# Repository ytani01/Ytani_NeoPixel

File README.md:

# Ytani NeoPixel Library

## 1. for Python3 on Raspberry Pi
  [rpi-python3/](rpi-python3/)

## 2. for C++ on Arduino, ESP32, ATTiny etc..
  [arduino-etc/](arduino-etc/)

### 2.0 !! 重要 !!

* NeoPixelライブラリの実行で、割り込みが効かなくなる
  ``show()``の直後に、``interrupts()`` または ``sei()``をすること！
* ATTiny85のメモリ(RAM)不足で、挙動がおかしくなる。

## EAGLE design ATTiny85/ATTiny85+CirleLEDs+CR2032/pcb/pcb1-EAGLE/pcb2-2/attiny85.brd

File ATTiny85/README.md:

# ATTiny85

## Arduio IEDによる書き込み

### ブートローダー

### ボード設定

- [ツール]-[ボード]-[ATTinyCore]-[ATTiny25/45/85 (No bootloader)]
- [ツール]-[Chip]-[ATTiny85]
- [ツール]-[書き込み装置]-[Arduino Leo/Micro as ISP (ATmega32U4)]

### ブートローダーの書き込み (最初の一回だけ)

- [ツール]-[ブートローダーを書き込む]

### 書き込み

- [スケッチ]-[書き込み装置を使って書き込む] (Ctrl+Shift+U)

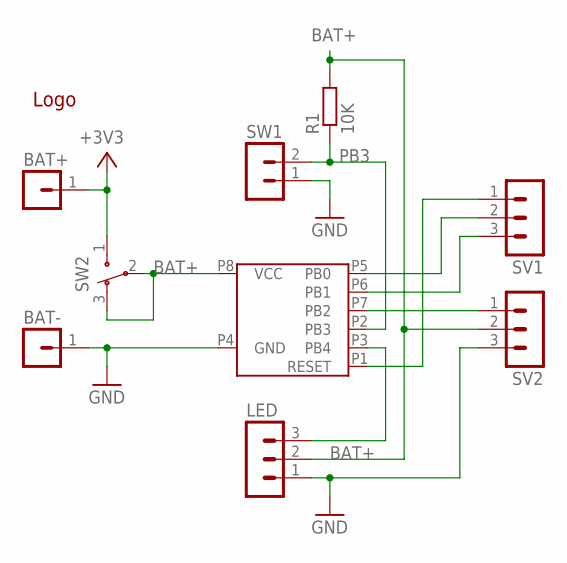
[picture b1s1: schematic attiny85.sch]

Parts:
ATTINY85-1: ATTINY85SOP8; ATTINY85-20SUR
BAT+: PINHEAD-MA01-1
BAT-: PINHEAD-MA01-1
LED: PINHEAD-MA03-1
LOGO1: LOGO-YTLOGO2-BOTTOM; LOGO-YT2-BOTTOM
R1: 10K; M3216
SV1, SV2: PINHEAD-MA03-1
SW1: PINHEAD-MA02-1
SW2: SW3-1

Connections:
+3V3: BAT+.1, SW2.1
BAT+: ATTINY85-1.P8 (VCC), LED.2, R1.2, SV2.2, SW2.2, SW2.3
GND: ATTINY85-1.P4 (GND), BAT-.1, LED.1, SV2.3, SW1.1
unnamed: ATTINY85-1.P3 (PB4), LED.3
unnamed: ATTINY85-1.P7 (PB2), SV2.1
unnamed: ATTINY85-1.P6 (PB1), SV1.3
unnamed: ATTINY85-1.P1 (RESET), SV1.1
unnamed: ATTINY85-1.P5 (PB0), SV1.2
PB3: ATTINY85-1.P2 (PB3), R1.1, SW1.2

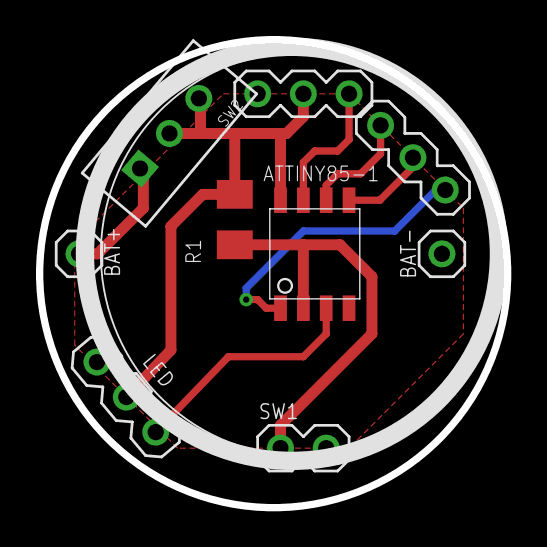
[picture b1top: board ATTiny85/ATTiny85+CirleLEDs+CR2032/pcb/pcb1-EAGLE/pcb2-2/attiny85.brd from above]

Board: 2 copper layers, 26.0 x 26.0 mm, 10 parts (0 on the bottom side), 9 nets.

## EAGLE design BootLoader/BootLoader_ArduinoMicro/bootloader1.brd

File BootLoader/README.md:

# PCB

## 1. 試作

### 1.1 ATTiny85

#### 1.1.1 [ATTiny85 + CirleLEDs + CR2032](ATTiny85/ATTiny85+CirleLEDs+CR2032/)

</img>
</img>
</img>

## 2. ブートローダー書き込み機

# 

# Appendix

## A.1 References

* [Arduino UNOでATtiny85を使う](http://www.hasshie765.server-on.net/wordpress/?p=1773)

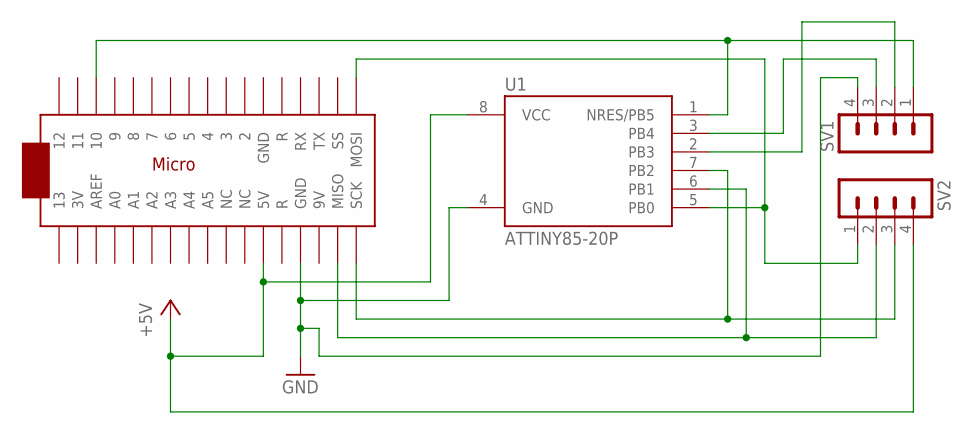
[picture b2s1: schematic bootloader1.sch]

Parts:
SV1, SV2: PINHEAD-MA04-1
U1: ATTINY85-20P; PDIP08_300MIL
U$1: ARDUINOMICRO

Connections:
+5V: SV2.4, U1.8 (VCC), U$1.P$23 (5V)
GND: SV1.4, U1.4 (GND), U$1.P$12 (GND)
unnamed: SV1.1, U1.1 (NRES/PB5), U$1.P$3 (10)
unnamed: SV2.3, U1.7 (PB2), U$1.P$18 (SCK)
unnamed: SV2.2, U1.6 (PB1), U$1.P$19 (MISO)
unnamed: SV2.1, U1.5 (PB0), U$1.P$17 (MOSI)
unnamed: SV1.3, U1.3 (PB4)
unnamed: SV1.2, U1.2 (PB3)

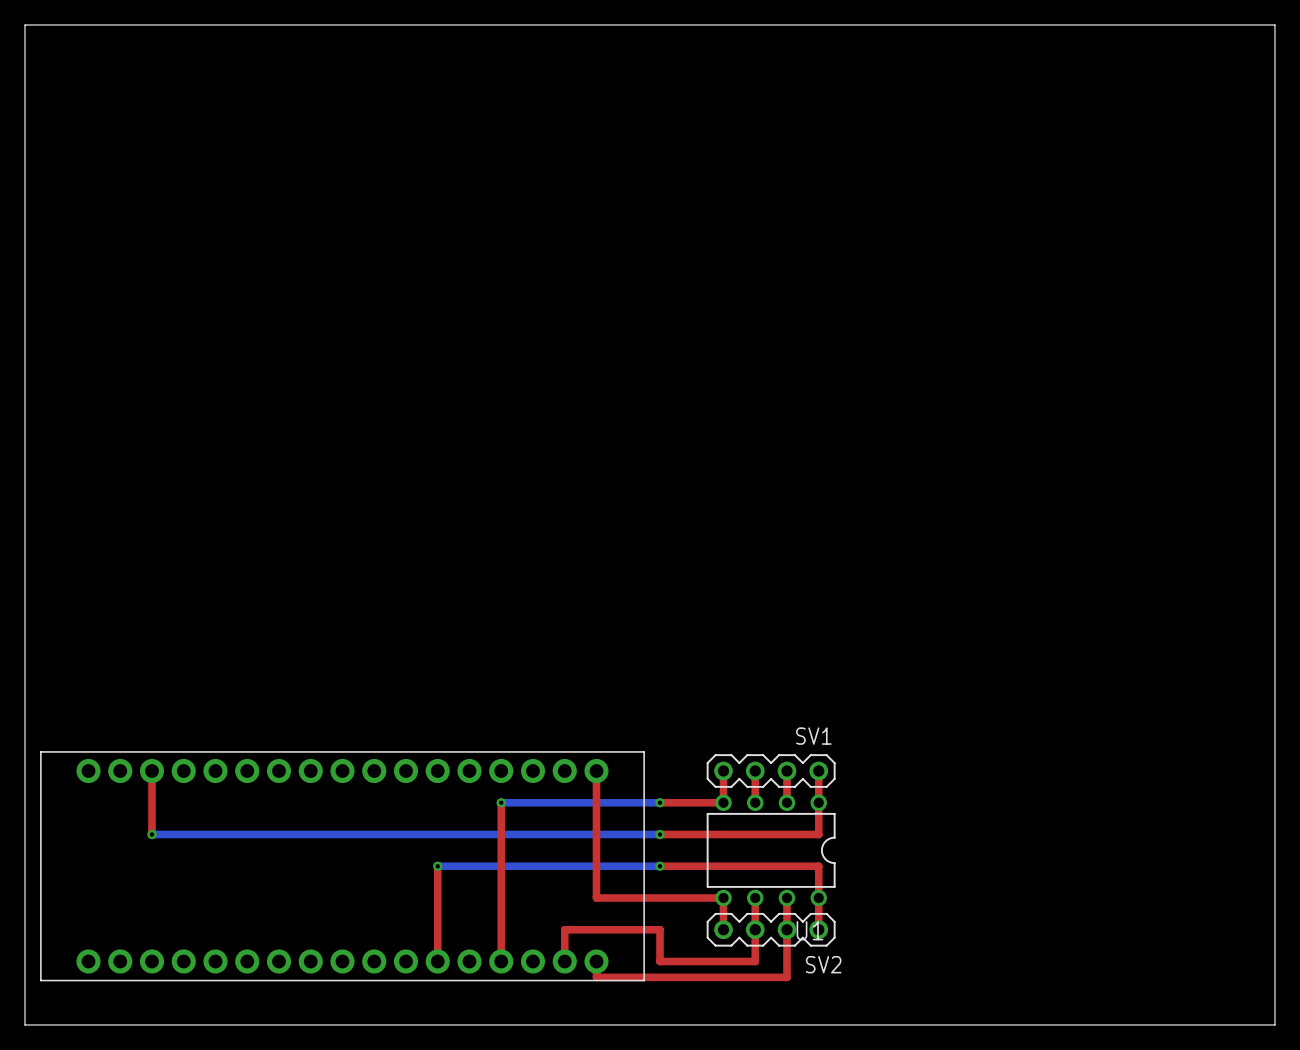
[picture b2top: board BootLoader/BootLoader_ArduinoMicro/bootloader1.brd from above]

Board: 2 copper layers, 100.0 x 80.0 mm, 4 parts (0 on the bottom side), 8 nets.

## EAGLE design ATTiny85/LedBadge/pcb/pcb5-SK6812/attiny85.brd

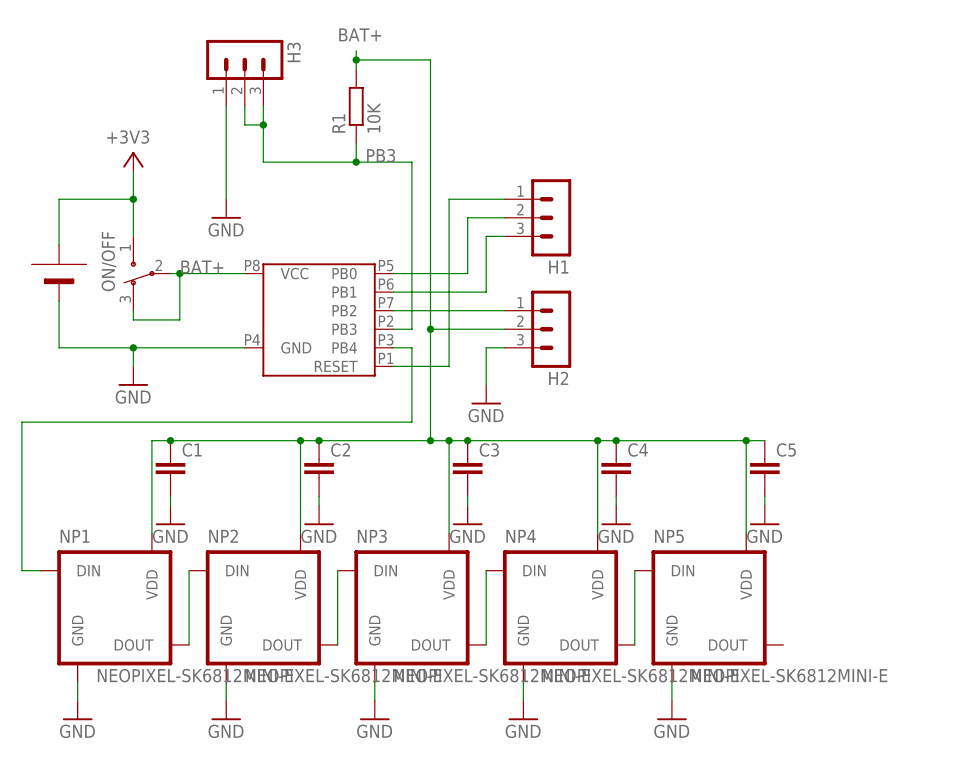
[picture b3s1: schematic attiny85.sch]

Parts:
ATTINY85-1: ATTINY85; ATTINY85-20SUR
BAT1: BAT-CR2032C; BAT-CR2032-3
C1, C2, C3, C4, C5: C-EUC2012; C2012
H1, H2: PINHEAD-MA03-1SMD; PINHEAD-MA03-2
H3: PINHEAD-MA03-1
NP1, NP2, NP3, NP4, NP5: NEOPIXEL-SK6812MINI-E; SK6812MINI-E
ON/OFF: POWER; SW3-1
R1: 10K; M3216

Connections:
+3V3: BAT1.V+ (BAT+), ON/OFF.1
BAT+: ATTINY85-1.P8 (VCC), C1.1, C2.1, C3.1, C4.1, C5.1, H2.2, NP1.VDD, NP2.VDD, NP3.VDD, NP4.VDD, NP5.VDD, ON/OFF.2, ON/OFF.3, R1.2
GND: ATTINY85-1.P4 (GND), BAT1.V-, C1.2, C2.2, C3.2, C4.2, C5.2, H2.3, H3.1, NP1.GND, NP2.GND, NP3.GND, NP4.GND, NP5.GND
unnamed: ATTINY85-1.P3 (PB4), NP1.DIN
unnamed: ATTINY85-1.P7 (PB2), H2.1
unnamed: ATTINY85-1.P6 (PB1), H1.3
unnamed: ATTINY85-1.P1 (RESET), H1.1
unnamed: ATTINY85-1.P5 (PB0), H1.2
unnamed: NP1.DOUT, NP2.DIN
unnamed: NP2.DOUT, NP3.DIN
unnamed: NP3.DOUT, NP4.DIN
unnamed: NP4.DOUT, NP5.DIN
PB3: ATTINY85-1.P2 (PB3), H3.2, H3.3, R1.1

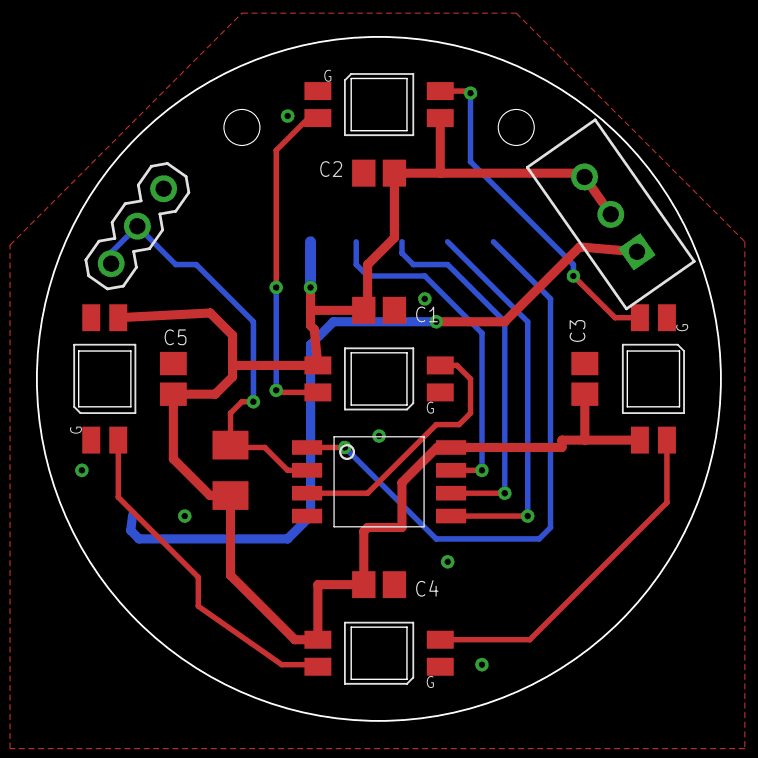
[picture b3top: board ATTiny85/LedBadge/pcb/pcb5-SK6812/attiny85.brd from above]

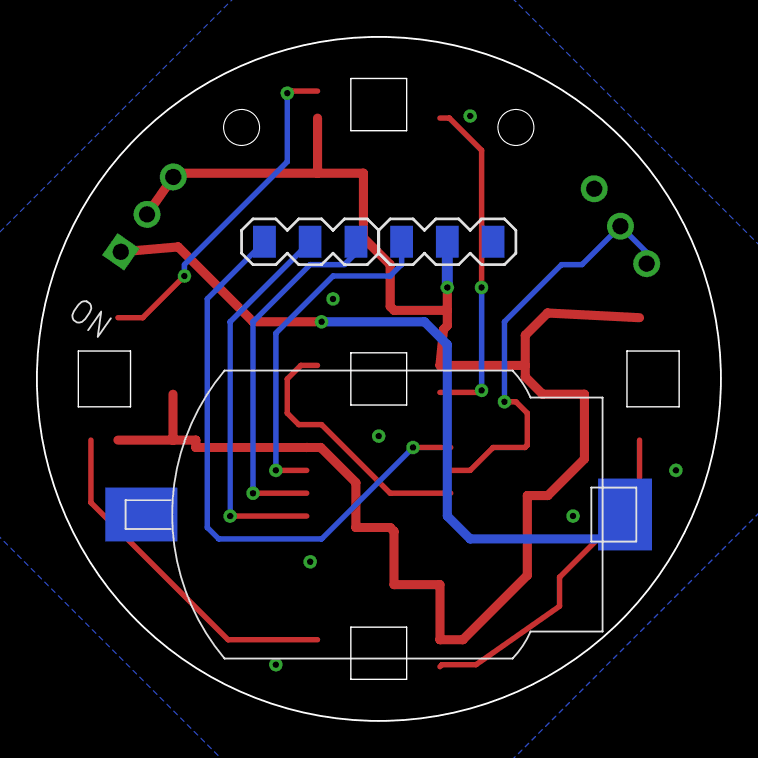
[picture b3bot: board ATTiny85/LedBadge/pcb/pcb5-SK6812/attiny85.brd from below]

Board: 2 copper layers, 38.0 x 38.0 mm, 17 parts (3 on the bottom side), 13 nets.

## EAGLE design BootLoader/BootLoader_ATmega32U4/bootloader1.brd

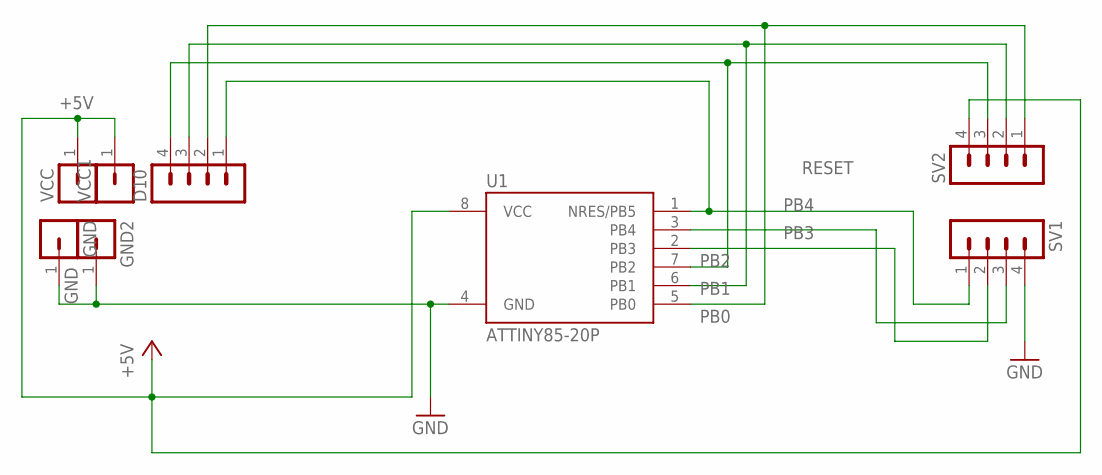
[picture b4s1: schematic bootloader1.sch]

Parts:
D10: PINHEAD-MA04-1
GND, GND2: PINHEAD-MA01-1
SV1, SV2: PINHEAD-MA04-1
U1: ATTINY85-20P; PDIP08_300MIL
VCC, VCC1: PINHEAD-MA01-1

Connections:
+5V: SV2.4, U1.8 (VCC), VCC.1, VCC1.1
GND: GND.1, GND2.1, SV1.4, U1.4 (GND)
PB0: D10.2, SV2.1, U1.5 (PB0)
PB1: D10.3, SV2.2, U1.6 (PB1)
PB2: D10.4, SV2.3, U1.7 (PB2)
PB3: SV1.2, U1.2 (PB3)
PB4: SV1.3, U1.3 (PB4)
RESET: D10.1, SV1.1, U1.1 (NRES/PB5)

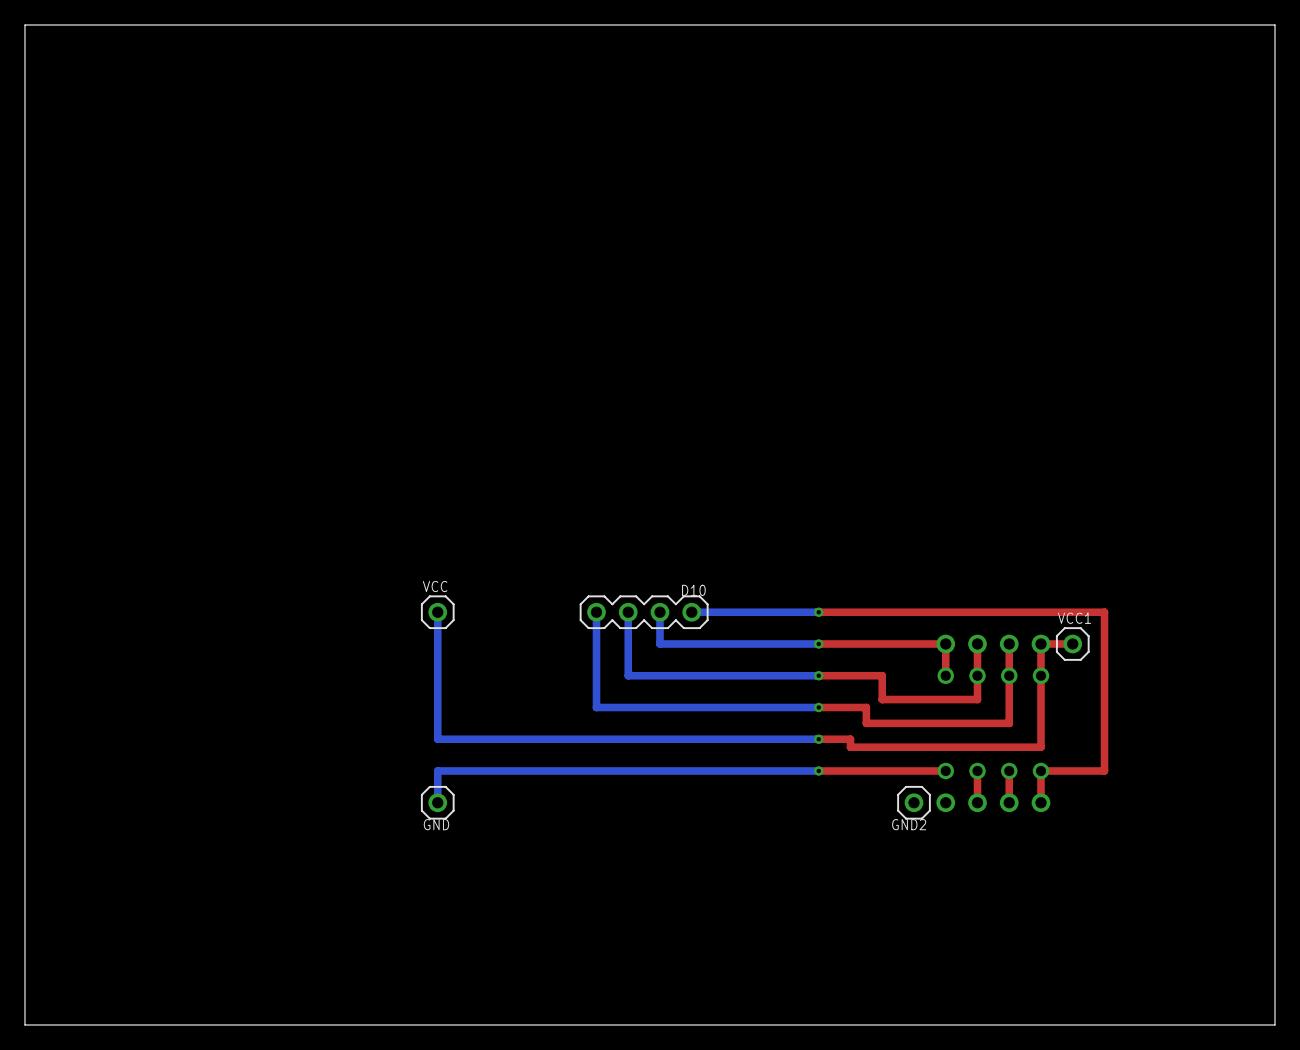
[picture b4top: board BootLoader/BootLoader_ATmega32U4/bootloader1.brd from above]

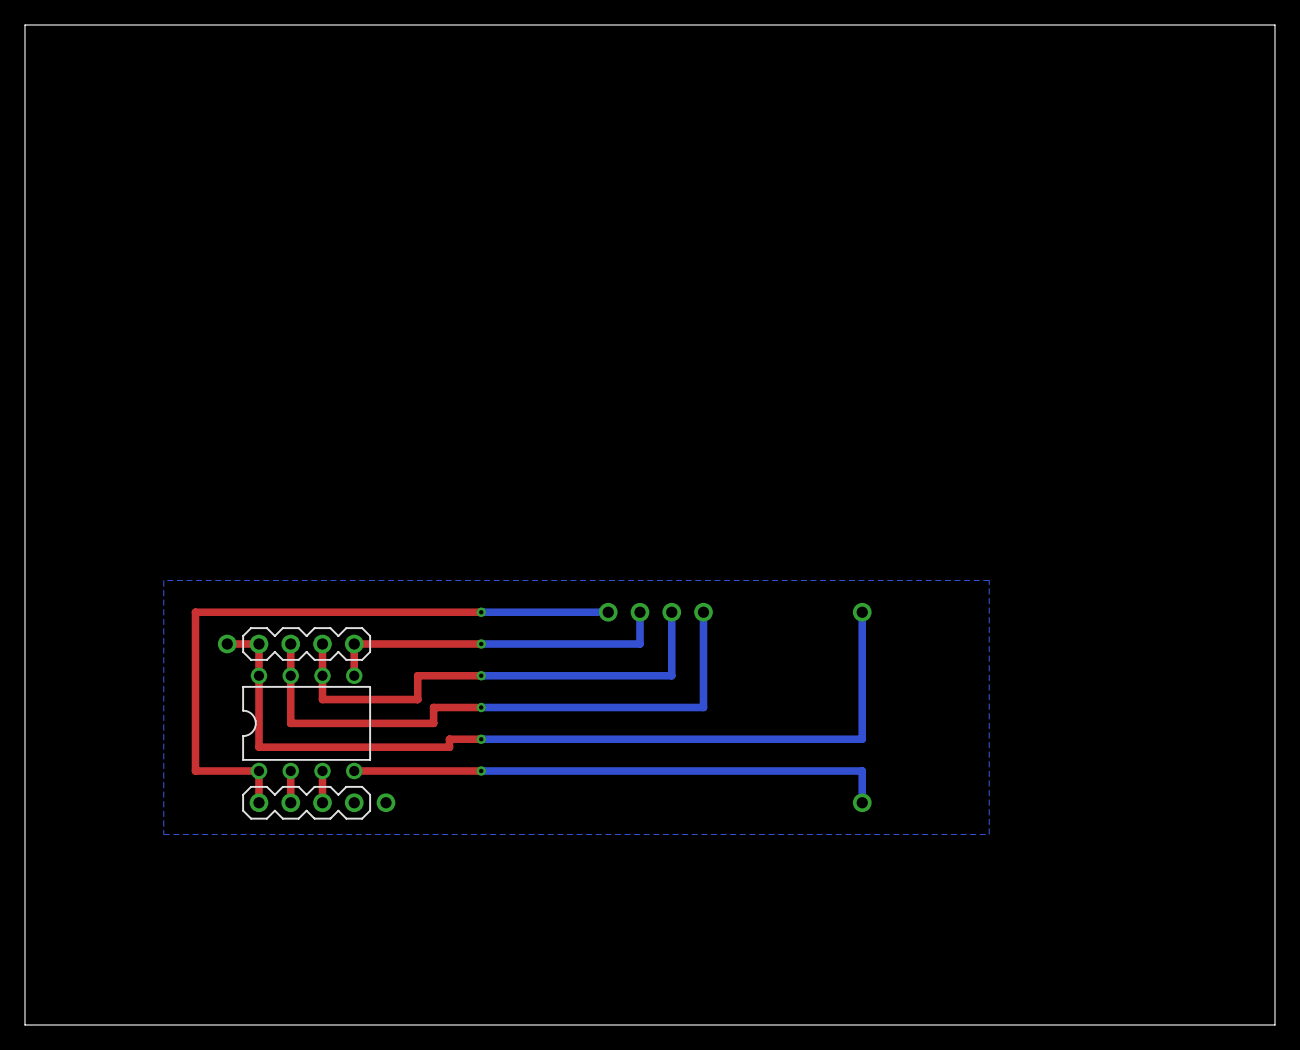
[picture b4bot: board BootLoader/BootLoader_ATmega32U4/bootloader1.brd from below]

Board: 2 copper layers, 100.0 x 80.0 mm, 8 parts (3 on the bottom side), 8 nets.

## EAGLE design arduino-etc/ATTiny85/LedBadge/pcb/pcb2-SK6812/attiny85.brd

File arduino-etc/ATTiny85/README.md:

# ATTiny85

## Arduio IEDによる書き込み

### ボード設定

- [ツール]-[ボード]-[ATTinyCore]-[ATTiny25/45/85 (No bootloader)]
- [ツール]-[Chip]-[ATTiny85]
- [ツール]-[書き込み装置]-[Arduino Leo/Micro as ISP (ATmega32U4)]

### ブートローダーの書き込み (最初の一回だけ)

- [ツール]-[ブートローダーを書き込む]

### 書き込み

- [スケッチ]-[書き込み装置を使って書き込む] (Ctrl+Shift+U)

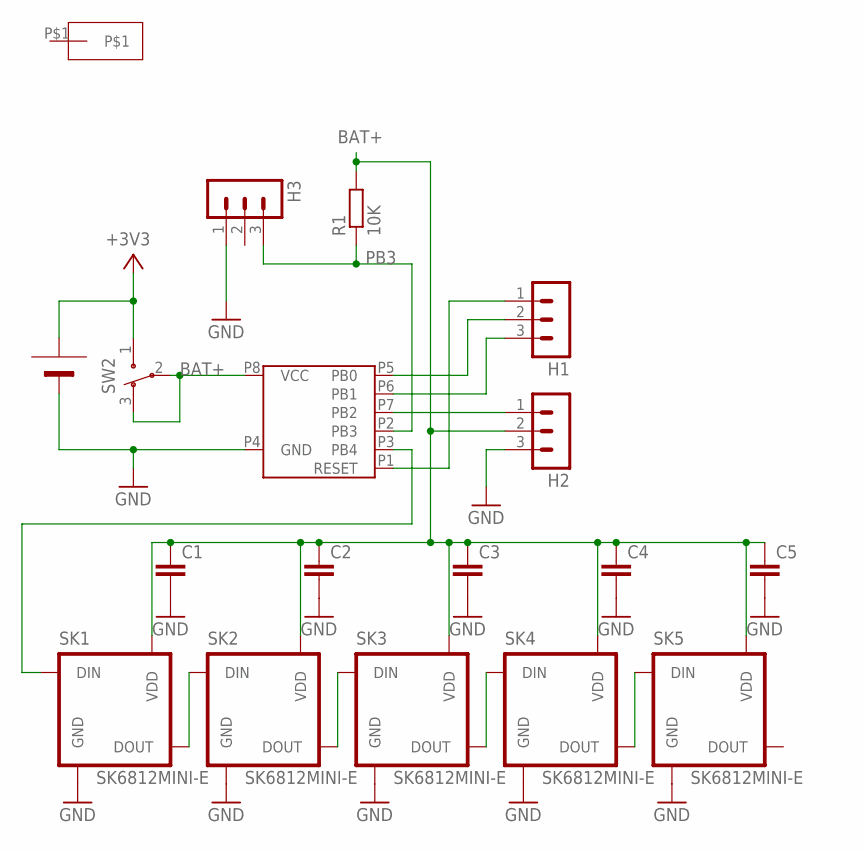
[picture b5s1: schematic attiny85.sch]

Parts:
ATTINY85-1: ATTINY85; ATTINY85-20SUR
BAT1: BAT-CR2032; BAT-CR2032-1
C1, C2, C3, C4, C5: C-EUC2012; C2012
H1, H2: PINHEAD-MA03-1SMD; PINHEAD-MA03-2
H3: PINHEAD-MA03-1
PAD33: PAD12X4; PAD-12X4
R1: 10K; M3216
SK1, SK2, SK3, SK4, SK5: SK6812MINI-E
SW2: POWER; SW3-1

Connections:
+3V3: BAT1.BAT+, SW2.1
BAT+: ATTINY85-1.P8 (VCC), C1.1, C2.1, C3.1, C4.1, C5.1, H2.2, R1.2, SK1.VDD, SK2.VDD, SK3.VDD, SK4.VDD, SK5.VDD, SW2.2, SW2.3
GND: ATTINY85-1.P4 (GND), BAT1.BAT-, C1.2, C2.2, C3.2, C4.2, C5.2, H2.3, H3.1, SK1.GND, SK2.GND, SK3.GND, SK4.GND, SK5.GND
unnamed: ATTINY85-1.P3 (PB4), SK1.DIN
unnamed: ATTINY85-1.P7 (PB2), H2.1
unnamed: ATTINY85-1.P6 (PB1), H1.3
unnamed: ATTINY85-1.P1 (RESET), H1.1
unnamed: ATTINY85-1.P5 (PB0), H1.2
unnamed: SK1.DOUT, SK2.DIN
unnamed: SK2.DOUT, SK3.DIN
unnamed: SK3.DOUT, SK4.DIN
unnamed: SK4.DOUT, SK5.DIN
PB3: ATTINY85-1.P2 (PB3), H3.3, R1.1

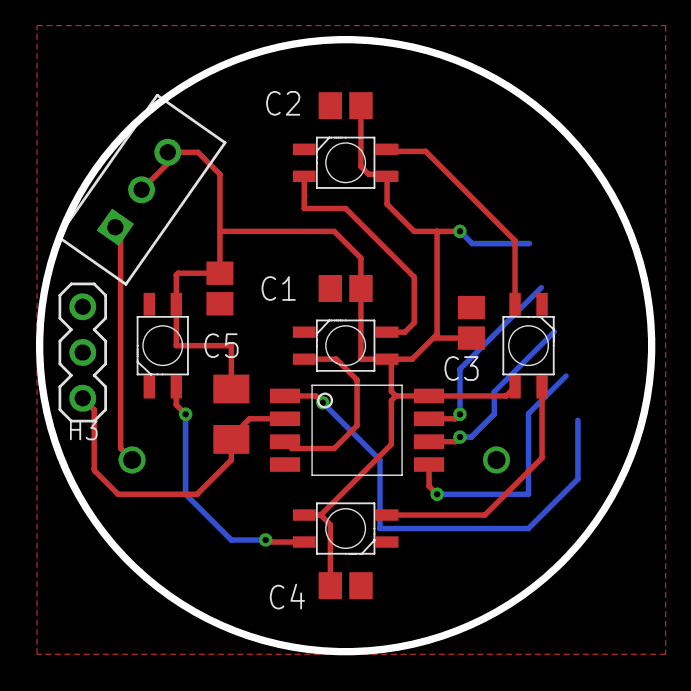
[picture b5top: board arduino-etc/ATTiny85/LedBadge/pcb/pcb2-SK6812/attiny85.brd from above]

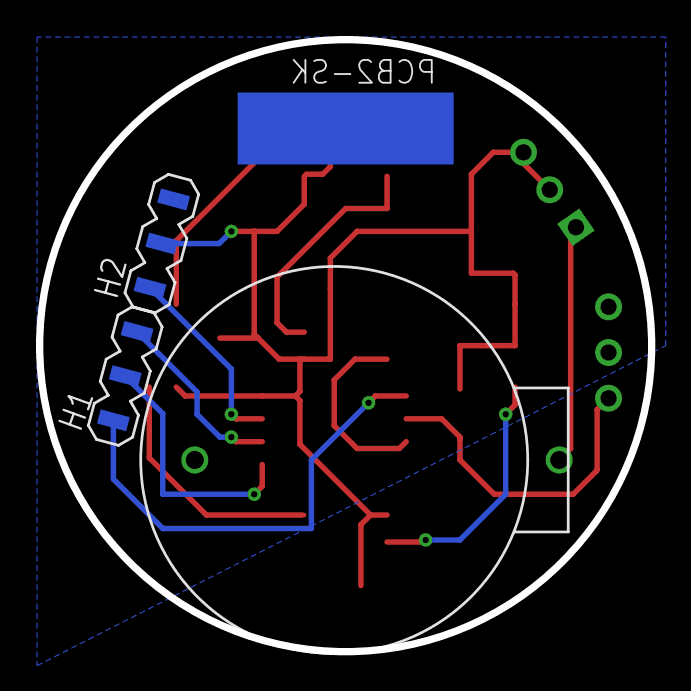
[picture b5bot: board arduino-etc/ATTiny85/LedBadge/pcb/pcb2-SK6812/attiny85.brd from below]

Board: 2 copper layers, 34.0 x 34.0 mm, 18 parts (4 on the bottom side), 13 nets.

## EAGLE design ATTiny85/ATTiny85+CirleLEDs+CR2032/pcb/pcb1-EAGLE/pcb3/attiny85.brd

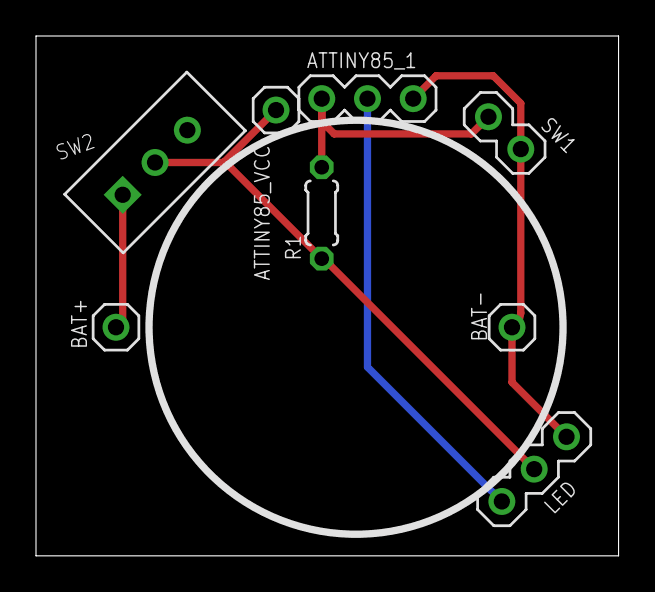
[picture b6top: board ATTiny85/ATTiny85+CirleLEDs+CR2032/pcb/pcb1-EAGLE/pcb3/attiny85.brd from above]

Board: 2 copper layers, 32.4 x 28.9 mm, 8 parts (0 on the bottom side), 5 nets.

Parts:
ATTINY85_1: PINHEAD-MA03-1
ATTINY85_VCC: PINHEAD-MA01-1
BAT+: PINHEAD-MA01-1
BAT-: PINHEAD-MA01-1
LED: PINHEAD-MA03-1
R1: 0204/5
SW1: PINHEAD-MA02-1
SW2: SW3-1

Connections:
+3V3: BAT+.1, SW2.1
BAT+: ATTINY85_VCC.1, LED.2, R1.2, SW2.2
GND: ATTINY85_1.1, BAT-.1, LED.1, SW1.1
PB3: ATTINY85_1.3, R1.1, SW1.2
PB4: ATTINY85_1.2, LED.3

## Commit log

2021-09-01 in preparation
2021-09-01 test1.py
2021-09-01 version 0.0.1
2021-09-01 UPD: README.md
2021-09-02 UPD: yt_neopixel.py
2021-09-02 UPD: rename
2021-09-02 UPD:
2021-09-02 ADD: test2
2021-09-02 UPD: __main__.py
2021-09-02 0.0.2
2021-09-02 START: 0.0.3
2021-09-02 ADD: Ytani_NeoPixel_Color class
2021-09-02 START: 0.0.4
2021-09-03 COMMIT: 0.0.4
2021-09-03 START: 0.0.5
2021-09-03 ADD: examples/robot_eye1.py
2021-09-05 UPD: tests
2021-09-05 START: 0.0.6
2021-09-05 ADD: class RobotEye_Cirle7LEDs
2021-09-05 START: 0.0.7
2021-09-06 UPD: class RobotEye_Cirle7LEDs
2021-09-06 UPD: robot_eyes_7leds.py
2021-09-06 FIX: install.sh
2021-09-06 START: 0.0.8
2021-09-06 ADD: RGB test
2021-09-06 START: 0.0.9
2021-09-06 UPD: for CuiLib 0.0.3
2021-09-06 START: 0.0.10
2021-09-06 START: 0.1.0
2021-09-07 UPD: README.md, setup.cfg
2021-09-10 START: 0.1.1
2021-09-12 UPD: add offset option to robot_eye1
2021-09-12 START: 0.1.2
2021-09-12 UPD: rgb-test
2021-09-12 START: 0.1.3
2021-09-13 UPD: robot_eye1
2021-09-13 START: 1.1.4
2021-09-13 START: 0.1.5
2021-09-15 UPD: update
2021-09-15 START: 1.1.6
2021-09-15 UPD: robot-eye
2021-09-16 UPD: dir tree
2021-09-16 ADD: arduino-c++
2021-09-18 ADD: color_wave2.ino
2021-09-18 UPD: color_wave2.ino
2021-09-20 UPD: demo
2021-09-20 UPD: robot_eye
2021-09-20 START: 0.1.7
2021-09-23 UPD: robot_eye_7leds.py
2021-09-25 ADD: Circle7LEDs-1.jpg
2021-09-28 START: 0.1.8
2021-09-28 ADD: interactive mode for robot-eye
2021-10-02 ADD: color_wave_4led/
2021-10-03 UPD: color_wave/
2021-10-05 ADD: tests/touch1
2021-10-06 UPD: tests/color_wave_ATTiny
2021-10-08 ADD: tests/switch1
2021-10-09 ADD: pcb
2021-10-09 ADD: pcb/bootloader
2021-10-09 UPD: .gitignore
2021-10-12 ADD: tests/color_wave3
2021-10-12 UPD: color_wave3
2021-11-18 UPD: pcb
2021-11-18 ADD: M5StampPico/
2021-11-18 ADD: M5StampPico/analogRead1/
2021-11-19 ADD: M5StampPico/sensor-NeoPixel/
2021-12-05 ADD: badge1/
2021-12-06 ADD: switch2/
2021-12-06 ADD: ATTiny-pinout.jpg
2021-12-07 ADD: switch3
2021-12-07 ADD: Mode_SingleColor
2021-12-07 UPD: switch3/
2021-12-10 ADD: pcb2/
2021-12-11 ADD: pcb3/
2021-12-12 ADD: LedLight2/
2021-12-12 UPD: LedLight2/
2021-12-13 ADD: LedLight3/Mode_White
2021-12-14 UPD: LedLight3/
2021-12-18 UPD: init.el
2021-12-20 ADD: ATTiny85/.../pcb2-2/
2021-12-22 ADD: LedLight4/
2021-12-22 UPD: LedLight4/ .. EEPROM
2021-12-22 UPD: rename LedLight4/ to LedLight/
2021-12-23 ADD: LedLight/Mode_Random1
2021-12-23 UPD: LedLight/Mode_Random1
2021-12-24 UPD: LedLight/
2022-01-13 START: LedLight3/
2022-01-13 ADD: pcb2-3/
2022-01-14 ADD: LedLight3/
2022-01-15 UPD: M5StampPico/color_wave3/
2022-01-15 ADD: M5StampPico/temp_sensor1/
2022-01-16 UPD: M5StampPico/temp_sensor1/
2022-03-19 START: LedLight4/
2022-05-24 DEL: pcb2-4/attiny85.brd
2022-05-24 ADD: LedLight5/
2022-10-16 ADD: pcb4-SK6812/
2022-10-16 FIX: pcb4-SK6812/
2022-10-16 ADD: sensor-NeoPixel2/
2022-10-28 UPD: ATTiny85/color_wave/
2022-10-29 UPD: ATTiny85/
2022-10-29 UPD: ATTiny85/LedBadge/
2022-10-30 UPD: pcb2-SK6812/
2022-10-30 UPD: LedBadge2/
2022-11-06 ADD: LedBudge3/
2022-11-06 UPD: LedBudge3-*/
2022-11-09 UPD: LedBadge3-../
2022-11-09 UPD: pcb3-../
2022-11-17 ADD:ATTiny85/README.md
2022-12-03 ADD: LedBadge/image
2022-12-04 ADD: sensor-NeoPixel-simpole1
2023-01-07 plate1.svg
2023-01-07 image/pcb4.*
2023-01-07 pcb4-SK6812/pcb4.*
2023-01-09 UPD: pcb4-SK6812/
2023-01-13 UPD: directory tree
2023-01-13 UPD: pcb4-SK6812/pcb4.svg
2023-01-14 UPD: pcb4-SK6812/pcb4.pdf
2023-01-14 UPD: pcb4-SK6812/pcb4.svg:
2023-01-15 ADD: LedTimer/
2023-06-10 modeSetTimer
2023-06-10 ADD: pcb5-SK6812
2023-06-22 pcb5
2025-06-11 ADD: ATTiny85 .. pcb2-3-KiCad
2025-06-12 UPD: directory tree: pcb/
